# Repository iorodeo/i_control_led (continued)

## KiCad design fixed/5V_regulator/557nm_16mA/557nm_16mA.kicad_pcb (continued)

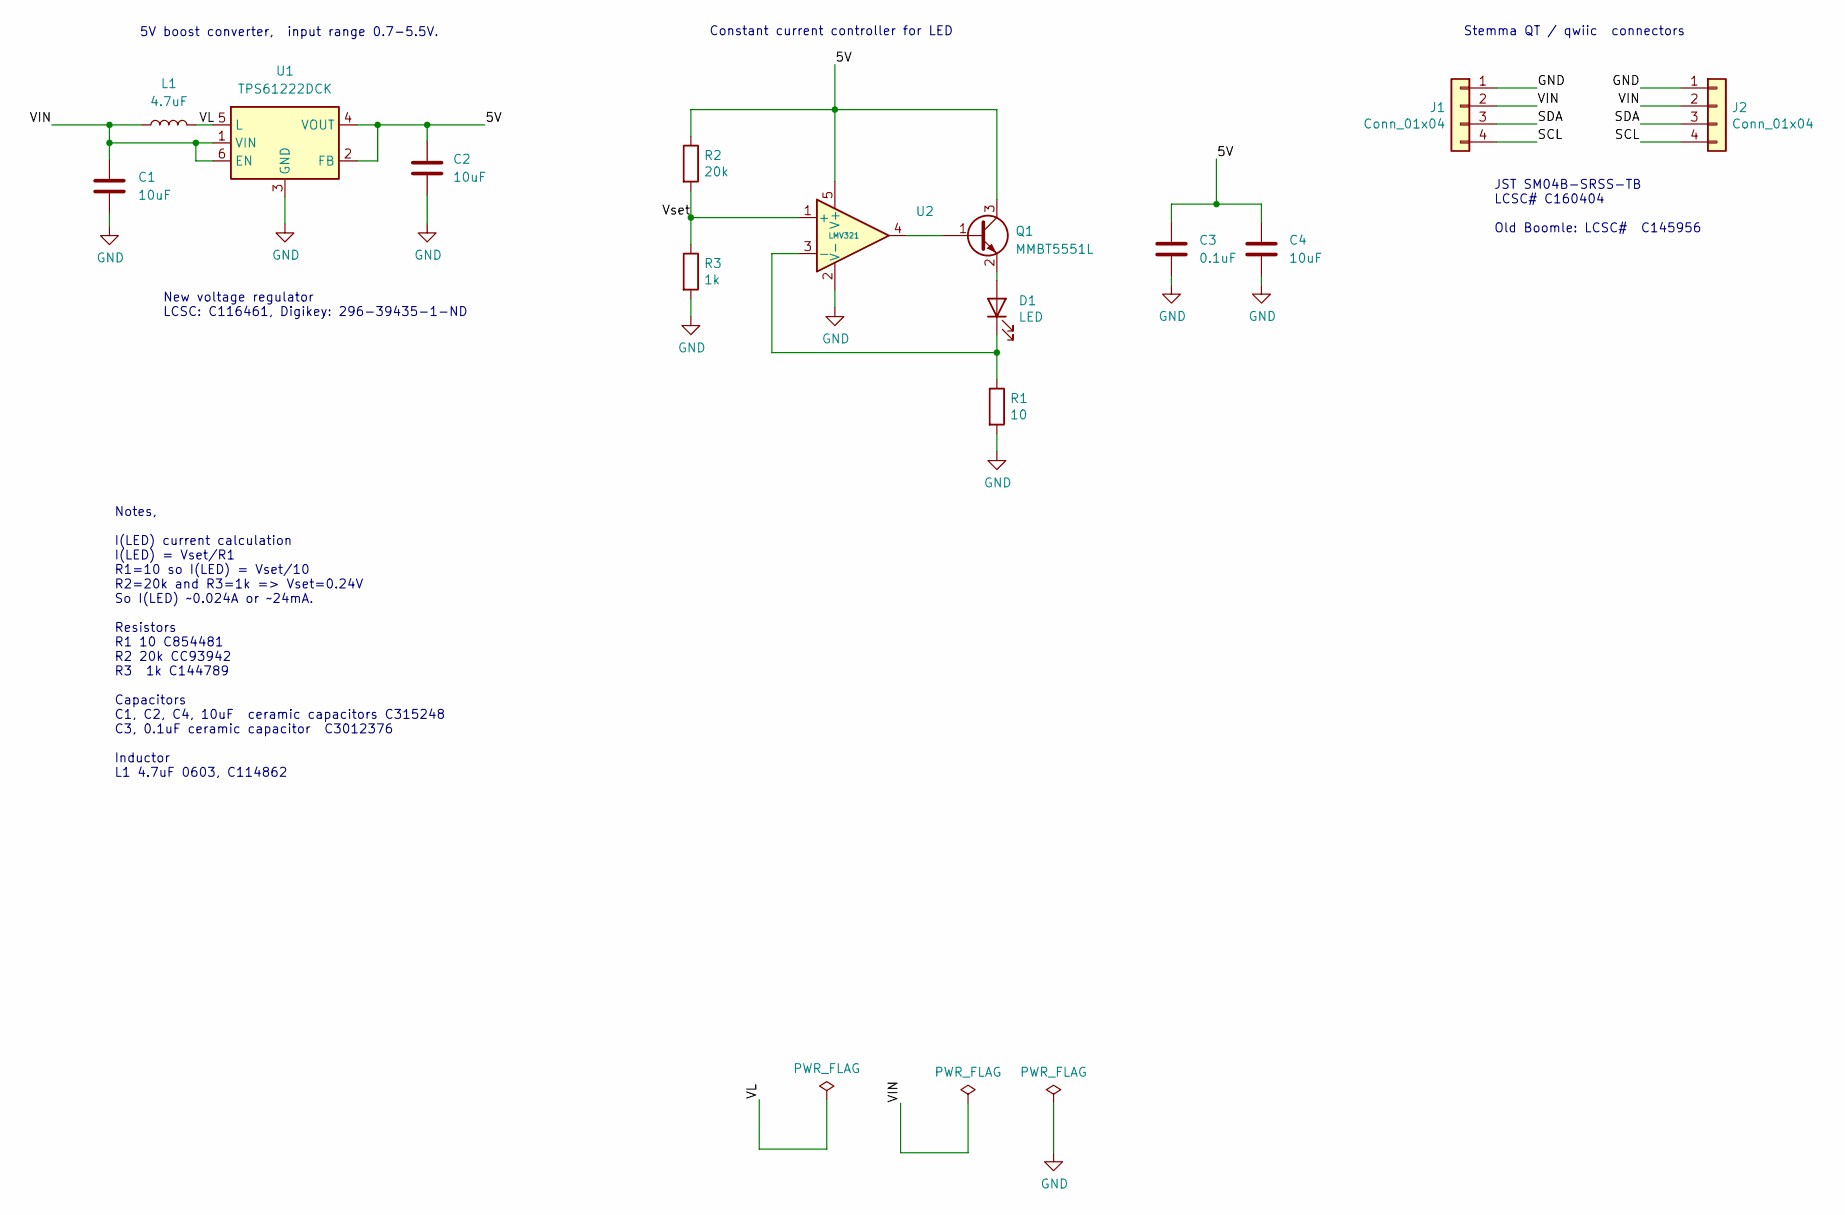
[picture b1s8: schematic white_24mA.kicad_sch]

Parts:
C1, C2, C4: 10uF; C_0402_1005Metric
C3: 0.1uF; C_0402_1005Metric
D1: LED; LED_0603_1608Metric
J1, J2: Conn_01x04; JST_SH_SM04B-SRSS-TB_1x04-1MP_P1.00mm_Horizontal
L1: 4.7uF; L_0603_1608Metric
Q1: MMBT5551L; SOT-23
R1: 10; R_0402_1005Metric
R2: 20k; R_0402_1005Metric
R3: 1k; R_0402_1005Metric
U1: TPS61222DCK; SOT-363_SC-70-6
U2: LMV321; SOT-23-5

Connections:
/5V: C2.2, C3.1, C4.1, Q1.3 (C), R2.1, U1.2 (FB), U1.4 (VOUT), U2.5 (V+)
/SCL: J1.4, J2.4
/SDA: J1.3, J2.3
/VIN: C1.2, J1.2, J2.2, L1.1, U1.1 (VIN), U1.6 (EN)
/VL: L1.2, U1.5 (L)
/Vset: R2.2, R3.1, U2.1 (+)
GND: C1.1, C2.1, C3.2, C4.2, J1.1, J2.1, R1.2, R3.2, U1.3 (GND), U2.2 (V-)
unnamed: D1.2 (A), Q1.2 (E)
unnamed: D1.1 (K), R1.1, U2.3 (-)
unnamed: Q1.1 (B), U2.4

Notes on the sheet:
JST SM04B-SRSS-TB LCSC# C160404 Old Boomle: LCSC# C145956
Stemma QT / qwiic connectors
New voltage regulator LCSC: C116461, Digikey: 296-39435-1-ND
Constant current controller for LED
5V boost converter, input range 0.7-5.5V.
Notes, I(LED) current calculation I(LED) = Vset/R1 R1=10 so I(LED) = Vset/10 R2=20k and R3=1k => Vset=0.24V So I(LED) ~0.024A or ~24mA. Resistors R1 10 C854481 R2 20k CC93942 R3 1k C144789 Capacitors C1, C2, C4, 10uF ceramic capacitors C315248 C3, 0.1uF ceramic capacitor C3012376 Inductor L1 4.7uF 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

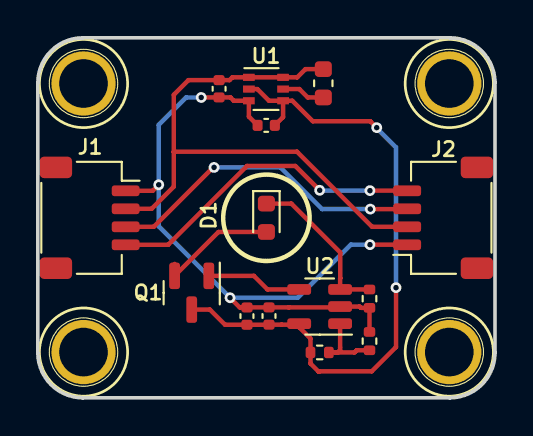
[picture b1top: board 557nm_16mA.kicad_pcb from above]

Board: 2 copper layers, 25.4 x 20.0 mm, 18 parts (0 on the bottom side), 10 nets.

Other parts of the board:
M1, M2, M3, M4: MountingHole_2.5mm_Pad

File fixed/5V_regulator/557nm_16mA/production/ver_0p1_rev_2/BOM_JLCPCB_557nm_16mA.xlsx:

Comment | Designator | Footprint | LCSC Part #（optional） | Qty
10V 10μF Ceramic Capacitor | C1,C2 C4 | 0402 | C315248 | 3
16V 100nF Ceramic Capacitor | C3 | 0402 | C3012376 | 1
LED (557nm) | D1 | 0603 | C6466138 | 1
4-Pin Connector, JST SM04B-SRSS-TB | J1 ,J2 | SMD,P=1mm | C160404 | 2
4.7μH Inductor ±20%, 440mOhm | L1 | 0603 | C114862 | 1
MMBT5551LT1G Bipolar Transistor, 600mA NPN | Q1 | SOT-23 | C41095 | 1
10Ω ±1% Resistor | R1 | 0402 | C413044 | 1
30kΩ ±1% Resistor | R2 | 0402 | C138008 | 1
1kΩ ±1% Resistor | R3 | 0402 | C144789 | 1
TPS61222DCKR, boost converter, fixed 5V | U1 | SOT-363-6(SC-70-6) | C116461 | 1
LMV321 Operational Amplifier | U2 | SOT-23-5 | C686637 | 1
